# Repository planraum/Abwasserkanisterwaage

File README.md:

# Abwasserkanisterwaage
documentary of the waste water weight scale

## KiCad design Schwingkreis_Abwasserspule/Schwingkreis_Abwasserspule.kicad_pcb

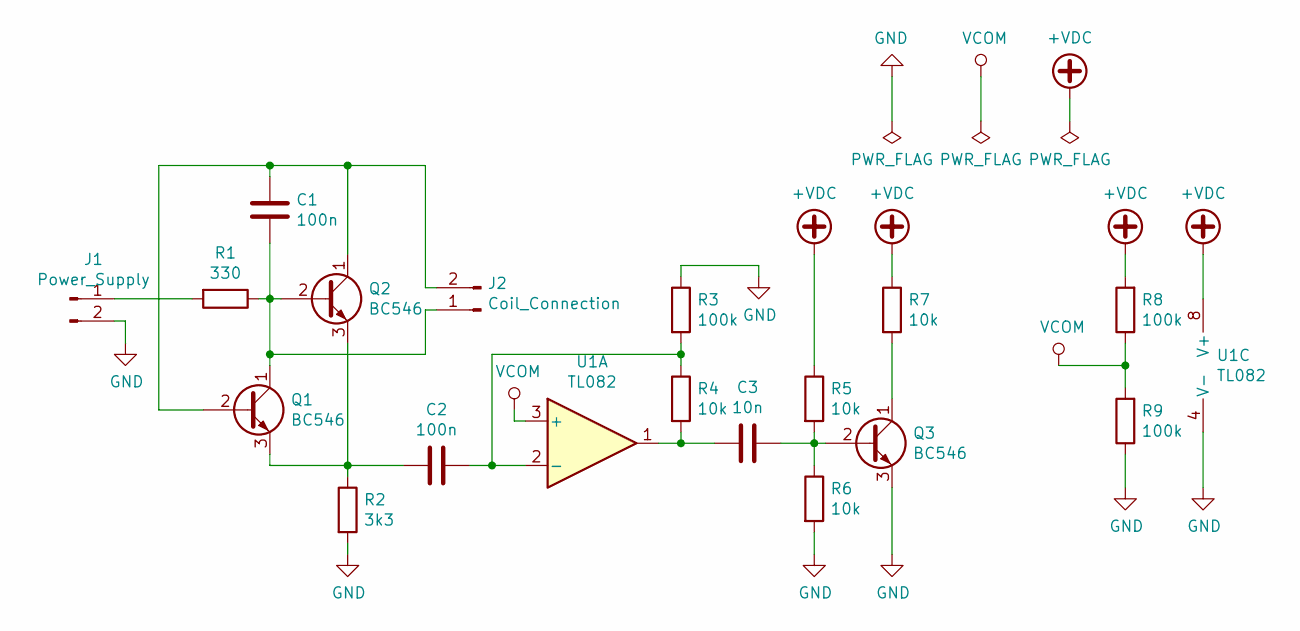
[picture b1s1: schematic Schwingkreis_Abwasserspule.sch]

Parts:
C1, C2: 100n; C_Rect_L7.2mm_W2.5mm_P5.00mm_FKS2_FKP2_MKS2_MKP2
C3: 10n; C_Rect_L9.0mm_W2.5mm_P7.50mm_MKT
J1: Power_Supply; PinHeader_1x02_P2.54mm_Vertical
J2: Coil_Connection; PinHeader_1x02_P2.54mm_Vertical
Q1, Q2, Q3: BC546; TO-92_Inline
R1: 330; R_Axial_DIN0207_L6.3mm_D2.5mm_P7.62mm_Horizontal
R2: 3k3; R_Axial_DIN0207_L6.3mm_D2.5mm_P7.62mm_Horizontal
R3, R8, R9: 100k; R_Axial_DIN0207_L6.3mm_D2.5mm_P7.62mm_Horizontal
R4, R5, R6, R7: 10k; R_Axial_DIN0207_L6.3mm_D2.5mm_P7.62mm_Horizontal
U1: TL082; DIP-8_W7.62mm_LongPads

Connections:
+VDC: R5.1, R7.1, R8.2, U1.8 (V+)
GND: J1.2, Q3.3 (E), R2.2, R3.1, R6.2, R9.1, U1.4 (V-)
unnamed: C1.1, J2.2, Q1.2 (B), Q2.1 (C)
unnamed: C1.2, J2.1, Q1.1 (C), Q2.2 (B), R1.1
unnamed: C2.1, R3.2, R4.1, U1.2 (-)
unnamed: C2.2, Q1.3 (E), Q2.3 (E), R2.1
unnamed: C3.1, Q3.2 (B), R5.2, R6.1
unnamed: C3.2, R4.2, U1.1
unnamed: J1.1, R1.2
unnamed: Q3.1 (C), R7.2
VCOM: R8.1, R9.2, U1.3 (+)

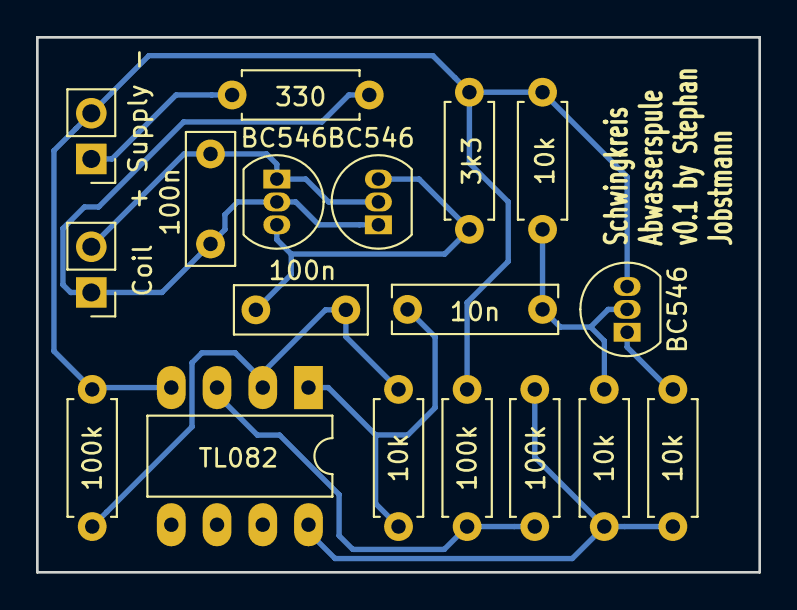
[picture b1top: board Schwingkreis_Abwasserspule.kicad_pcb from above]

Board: 2 copper layers, 40.1 x 29.7 mm, 18 parts (0 on the bottom side), 11 nets.

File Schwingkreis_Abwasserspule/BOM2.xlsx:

Spalte1 | Spalte2 | Spalte3 | Spalte4
C1 | 100n |  | ~
C2 | 100n |  | ~
C3 | 10n |  | ~
J1 | Power_Supply |  | ~
J2 | Coil_Connection |  | ~
Q1 | BC546 | Package_TO_SOT_THT:TO-92_Inline | http://www.fairchildsemi.com/ds/BC/BC547.pdf
Q2 | BC546 | Package_TO_SOT_THT:TO-92_Inline | http://www.fairchildsemi.com/ds/BC/BC547.pdf
Q3 | BC546 | Package_TO_SOT_THT:TO-92_Inline | http://www.fairchildsemi.com/ds/BC/BC547.pdf
R1 | 330 |  | ~
R2 | 3k3 |  | ~
R3 | 100k |  | ~
R4 | 10k |  | ~
R5 | 10k |  | ~
R6 | 10k |  | ~
R7 | 10k |  | ~
R8 | 100k |  | ~
R9 | 100k |  | ~
U1 | TL082 |  | http://www.ti.com/lit/ds/symlink/tl081.pdf

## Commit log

2019-04-29 added the KiCAD files of the resonator circuit. Schematic is done, layout is raw.
2019-05-06 final design for this version. ordered 5 times at jlcpcb
